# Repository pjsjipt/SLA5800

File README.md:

# SLA5800
Software and electronics to control the SLA5800 thermal mass flow controlers

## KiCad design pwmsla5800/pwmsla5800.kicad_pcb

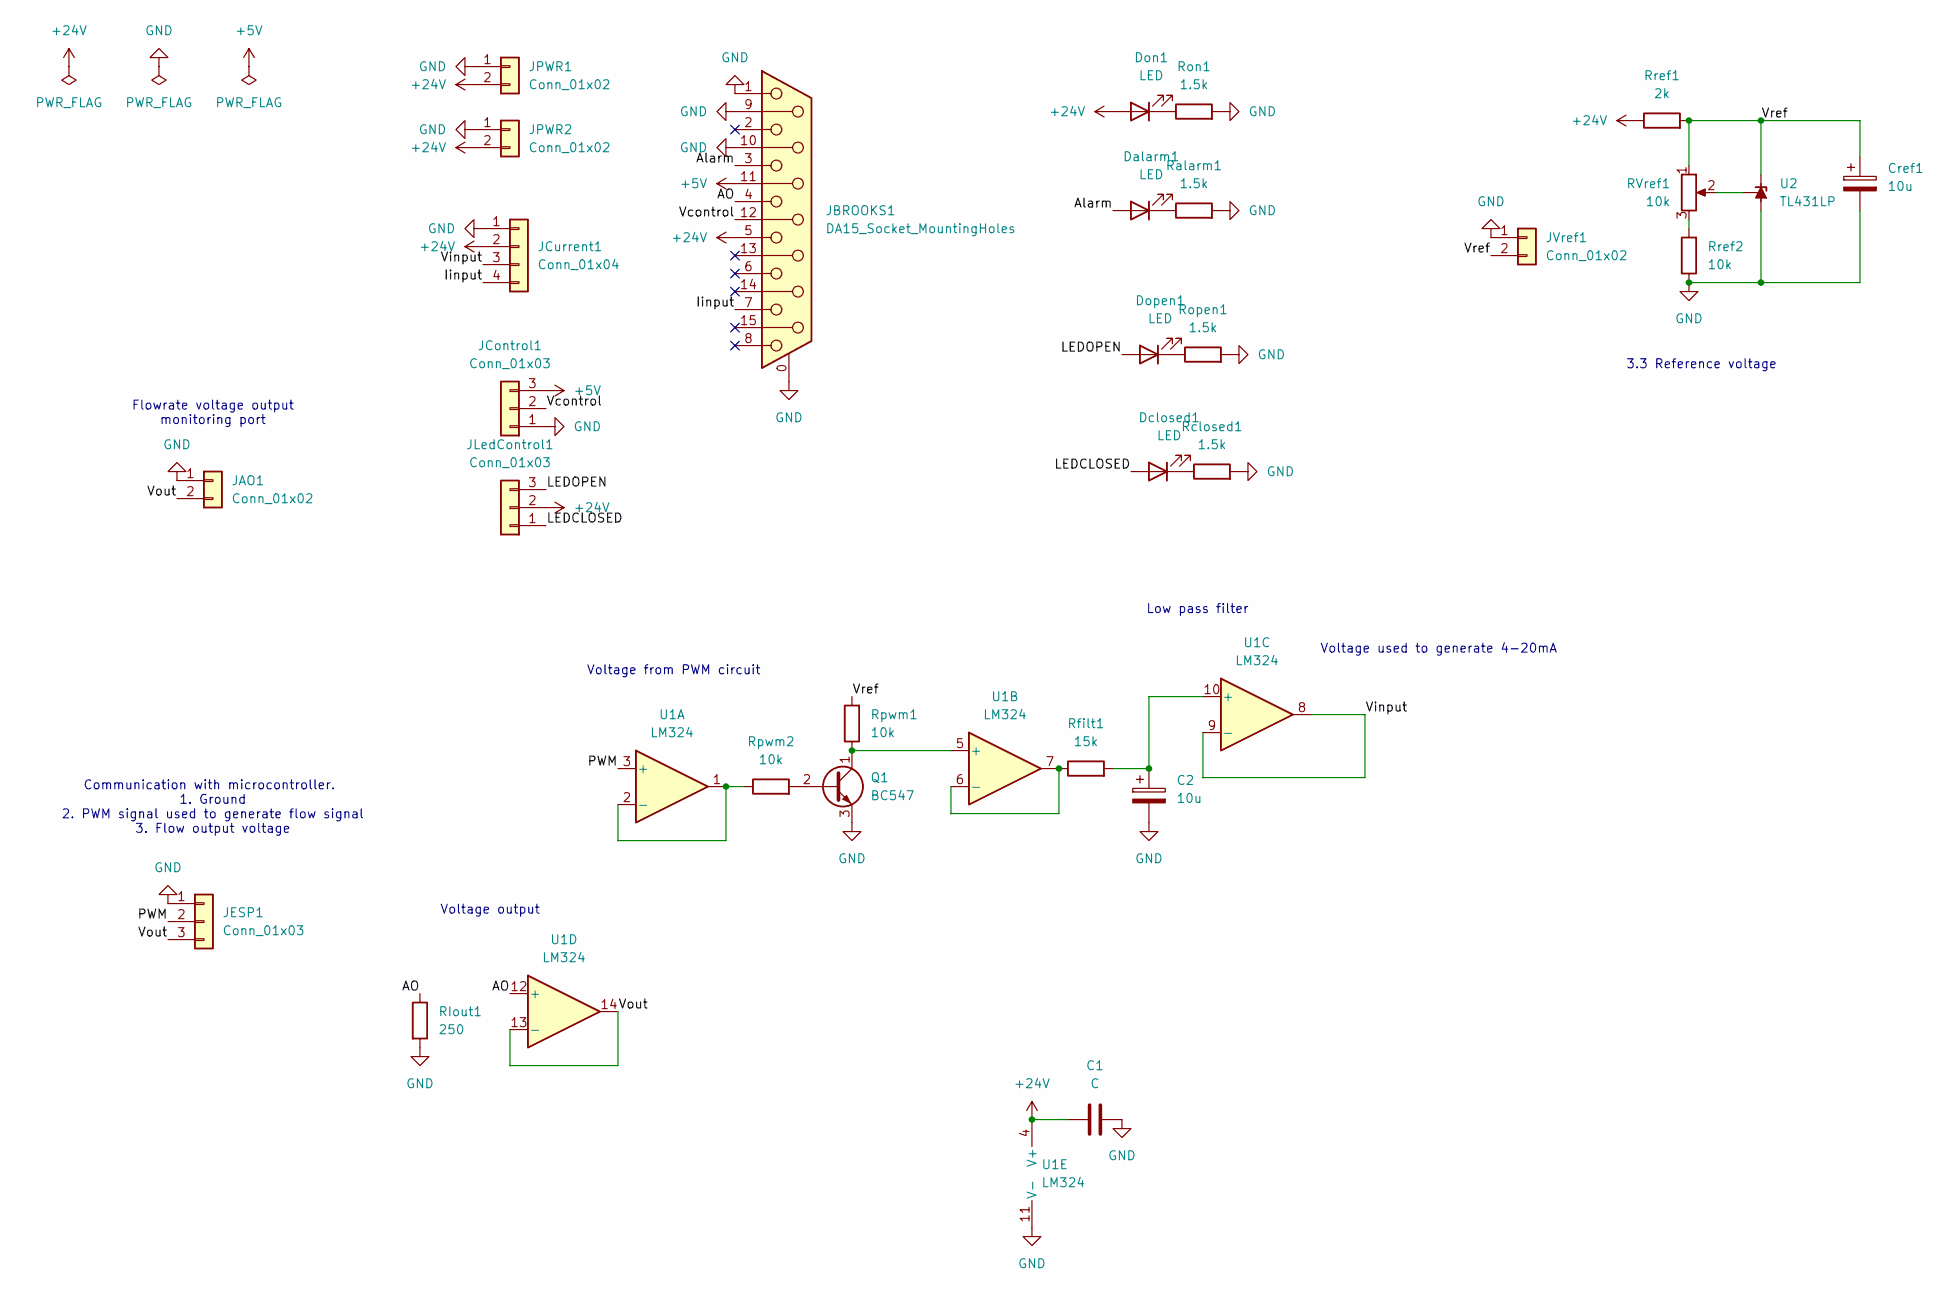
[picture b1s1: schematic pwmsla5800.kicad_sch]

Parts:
C1: C; C_Disc_D5.0mm_W2.5mm_P2.50mm
C2: 10u; CP_Radial_D6.3mm_P2.50mm
Cref1: 10u; CP_Radial_D6.3mm_P2.50mm
Dalarm1: LED; LED_D3.0mm
Dclosed1: LED; LED_D3.0mm
Don1: LED; LED_D3.0mm
Dopen1: LED; LED_D3.0mm
JAO1: Conn_01x02; PinHeader_1x02_P2.54mm_Vertical
JBROOKS1: DA15_Socket_MountingHoles; DSUB-15_Socket_Horizontal_P2.77x2.84mm_EdgePinOffset7.70mm_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
JControl1: Conn_01x03; PinHeader_1x03_P2.54mm_Vertical
JCurrent1: Conn_01x04; PinHeader_1x04_P2.54mm_Vertical
JESP1: Conn_01x03; PinHeader_1x03_P2.54mm_Vertical
JLedControl1: Conn_01x03; PinHeader_1x03_P2.54mm_Vertical
JPWR1, JPWR2: Conn_01x02; PhoenixContact_MSTBVA_2,5_2-G-5,08_1x02_P5.08mm_Vertical
JVref1: Conn_01x02; PinHeader_1x02_P2.54mm_Vertical
Q1: BC547; TO-92_Inline_Wide
RIout1: 250; R_Axial_DIN0207_L6.3mm_D2.5mm_P10.16mm_Horizontal
RVref1: 10k; Potentiometer_Bourns_3296W_Vertical
Ralarm1: 1.5k; R_Axial_DIN0207_L6.3mm_D2.5mm_P10.16mm_Horizontal
Rclosed1: 1.5k; R_Axial_DIN0207_L6.3mm_D2.5mm_P10.16mm_Horizontal
Rfilt1: 15k; R_Axial_DIN0207_L6.3mm_D2.5mm_P10.16mm_Horizontal
Ron1: 1.5k; R_Axial_DIN0207_L6.3mm_D2.5mm_P10.16mm_Horizontal
Ropen1: 1.5k; R_Axial_DIN0207_L6.3mm_D2.5mm_P10.16mm_Horizontal
Rpwm1, Rpwm2: 10k; R_Axial_DIN0207_L6.3mm_D2.5mm_P10.16mm_Horizontal
Rref1: 2k; R_Axial_DIN0207_L6.3mm_D2.5mm_P10.16mm_Horizontal
Rref2: 10k; R_Axial_DIN0207_L6.3mm_D2.5mm_P10.16mm_Horizontal
U1: LM324; CERDIP-14_W7.62mm_SideBrazed_LongPads_Socket
U2: TL431LP; TO-92_Inline_Wide

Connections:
+5V: JBROOKS1.11 (P111), JControl1.3
+24V: C1.1, Don1.2 (A), JBROOKS1.5, JCurrent1.2, JLedControl1.2, JPWR1.2, JPWR2.2, Rref1.1, U1.4 (V+)
/AO: JBROOKS1.4, RIout1.1, U1.12 (+)
/Alarm: Dalarm1.2 (A), JBROOKS1.3
/Iinput: JBROOKS1.7, JCurrent1.4
/LEDCLOSED: Dclosed1.2 (A), JLedControl1.1
/LEDOPEN: Dopen1.2 (A), JLedControl1.3
/PWM: JESP1.2, U1.3 (+)
/Vcontrol: JBROOKS1.12, JControl1.2
/Vinput: JCurrent1.3, U1.8, U1.9 (-)
/Vout: JAO1.2, JESP1.3, U1.13 (-), U1.14
/Vref: Cref1.1, JVref1.2, RVref1.1, Rpwm1.2, Rref1.2, U2.3 (K)
GND: C1.2, C2.2, Cref1.2, JAO1.1, JBROOKS1.0 (PAD), JBROOKS1.1, JBROOKS1.9, JBROOKS1.10, JControl1.1, JCurrent1.1, JESP1.1, JPWR1.1, JPWR2.1, JVref1.1, Q1.3 (E), RIout1.2, Ralarm1.2, Rclosed1.2, Ron1.2, Ropen1.2, Rref2.1, U1.11 (V-), U2.2 (A)
unnamed: Dalarm1.1 (K), Ralarm1.1
unnamed: Dclosed1.1 (K), Rclosed1.1
unnamed: Don1.1 (K), Ron1.1
unnamed: Dopen1.1 (K), Ropen1.1
unnamed: Q1.2 (B), Rpwm2.2
unnamed: Q1.1 (C), Rpwm1.1, U1.5 (+)
unnamed: RVref1.3, Rref2.2
unnamed: Rpwm2.1, U1.1, U1.2 (-)
unnamed: Rfilt1.1, U1.6 (-), U1.7
unnamed: C2.1, Rfilt1.2, U1.10 (+)
unnamed: RVref1.2, U2.1 (REF)

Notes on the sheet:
Voltage from PWM circuit
3.3 Reference voltage
Voltage output
Low pass filter
Communication with microcontroller. 1. Ground 2. PWM signal used to generate flow signal 3. Flow output voltage
Flowrate voltage output monitoring port
Voltage used to generate 4-20mA

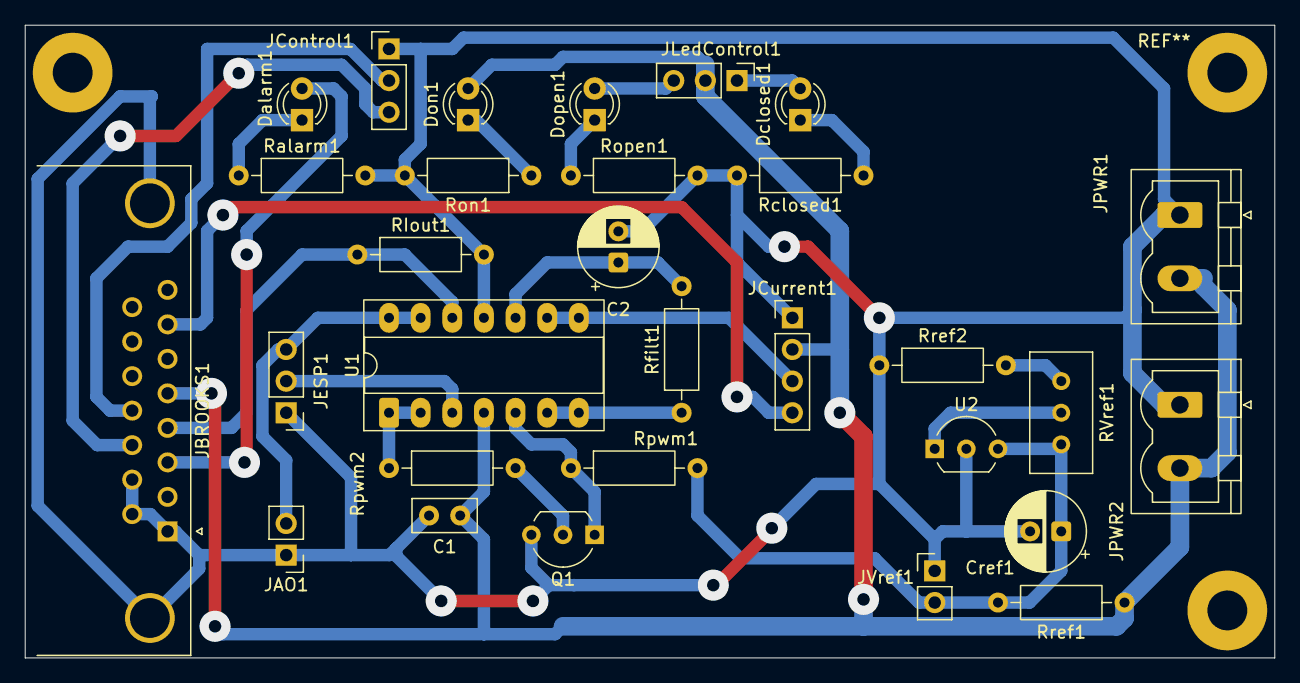
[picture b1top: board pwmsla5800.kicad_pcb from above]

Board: 2 copper layers, 100.3 x 50.8 mm, 30 parts (0 on the bottom side), 24 nets.

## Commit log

2025-07-30 Basic electronic circuit is, apparently, working.
    Current sources are trickier than they seem.
    Now I need to create the software for generating PWM
2025-07-30 Created the basic PlatformIO project for visual studio code.
    Nothing in the project (yet...).
2025-07-30 Started working on the code
2026-01-27 New concept. Generating the 4-20mA current is done on an outside module
    Until I figure out how generate the current well, I think it is better just use a Chinese board.
    When generating the PWM, to obtain a stable voltage I am using a TL431 circuit.
2026-02-01 Criando silk sem furos. Melhor na corrosão
2026-02-21 Worked a little on software
    Just saving because I'm going to make a bigger change in board layout.
2026-02-21 Added silks for 4 boards
    I'm trying to use the small drill marks. Let's see if this is better for making the board using the laser cutter and acid.
2026-03-04 Implemented the MQTT interface
    I simplified stuff a little bit. For now we can not select the channels without compiling the code again. It will read all channels simultaneously.
2026-03-04 Added MEAS topic
    This topic determines if the analog inputs should be read. If 1, the AI should be read. If 0 stop measuring.
2026-04-01 Corrected small bug in `pwm_mwtt.cpp` and updated R values in the board.
2026-05-02 Created gerber files for JLCPCB
